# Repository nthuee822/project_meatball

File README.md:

# project_meatball

A custom three-wheel omnidirectional robot: radial-mount wheels driven by
FOC-controlled motors with magnetic angle encoders, steered by a Logitech F710
gamepad through a Raspberry Pi, with IMU-based orientation sensing and
custom PCBs and 3D-printed mechanical parts.

## Repository Layout

| Directory | Contents |
|---|---|
| [`controller/`](controller/) | Raspberry Pi Python controller: reads the gamepad, computes inverse kinematics for the three radial wheels, and streams motor commands over SPI (optionally fused with IMU data). |
| [`IMU/`](IMU/) | Standalone Python driver for the ICM-20948 9-axis IMU (accel/gyro/mag) over I2C on the Raspberry Pi, plus calibration and debug scripts. |
| [`stm32/`](stm32/) | STM32CubeIDE firmware projects for the per-wheel motor drivers: field-oriented control (`foc_v0`, `foc_v1`), AS5600 magnetic encoder angle measurement (`angle_measurement_test`, `angle_measurement_kalman`), ADC alignment testing, and a stepper/SPI test build. `common_lib/` holds the shared AS5600 driver. |
| [`hardware/`](hardware/) | KiCad PCB projects: current-sense simulation, the `ht7k1401` breakout board, and a shared component library. |
| [`3d_model/`](3d_model/) | FreeCAD/3MF models for printed parts — motor holders, hall-sensor holders/washers, magnet mold, and corner brackets. |
| [`architecture/`](architecture/) | System architecture diagrams (drawio source + exported PDF). |
| [`images/`](images/) | Reference photos and renders. |

## System Overview

```
F710 gamepad --USB--> Raspberry Pi (controller/) --SPI--> STM32 motor drivers (stm32/foc_*)
                              ^                                    |
                              |                                    v
                        IMU/ (ICM-20948)                 AS5600 encoder + motor
```

Each wheel's STM32 board runs closed-loop FOC using position feedback from an
AS5600 magnetic encoder (angle read directly, or Kalman-filtered — see
`stm32/angle_measurement_kalman`). The Raspberry Pi computes per-wheel speed/
direction from gamepad input via radial-mount inverse kinematics and sends
them as fixed-format SPI frames; see [`controller/README.md`](controller/README.md)
for the protocol and kinematics details.

## Getting Started

### Python Environment (uv)

All Python code (`controller/`, `IMU/`, `stm32/*/` scripts) shares one
environment managed by [uv](https://docs.astral.sh/uv/), defined in
`pyproject.toml` and pinned by `uv.lock`. It lives in `.venv/` at the repo
root and does not touch your system Python.

```bash
# 1. Install uv (once per machine)
curl -LsSf https://astral.sh/uv/install.sh | sh          # Linux / macOS
# powershell -c "irm https://astral.sh/uv/install.ps1 | iex"   # Windows

# 2. Create .venv and install dependencies (re-run after pulling changes)
uv sync

# 3. Run scripts through uv (works from any subdirectory)
cd controller && uv run python run_test.py
```

Hardware libraries (`smbus2`, `spidev`, `rpi-lgpio` which provides
`RPi.GPIO`) are only installed on Raspberry Pi (Linux ARM64). On a laptop,
`uv sync` skips them, so you can still run the hardware-independent parts
(kinematics, gamepad/keyboard input, plotting).

On the Raspberry Pi, `rpi-lgpio` is compiled from source, so install the build
dependencies once before the first `uv sync`:

```bash
sudo apt install -y swig liblgpio-dev
```

To add a dependency: `uv add <package>` (commit both `pyproject.toml` and `uv.lock`).

### Subsystems

Each subsystem has its own setup instructions:

- Robot controller (gamepad + kinematics + SPI): [`controller/README.md`](controller/README.md)
- IMU driver and wiring/calibration: [`IMU/README.md`](IMU/README.md)
- STM32 firmware: open the relevant `.ioc` project in STM32CubeIDE (each project directory is self-contained with CMake presets for building outside the IDE).
- PCB designs: open the `.kicad_pro` files in KiCad.
- 3D models: open the `.FCStd` files in FreeCAD; `.3mf` files are ready to slice/print.

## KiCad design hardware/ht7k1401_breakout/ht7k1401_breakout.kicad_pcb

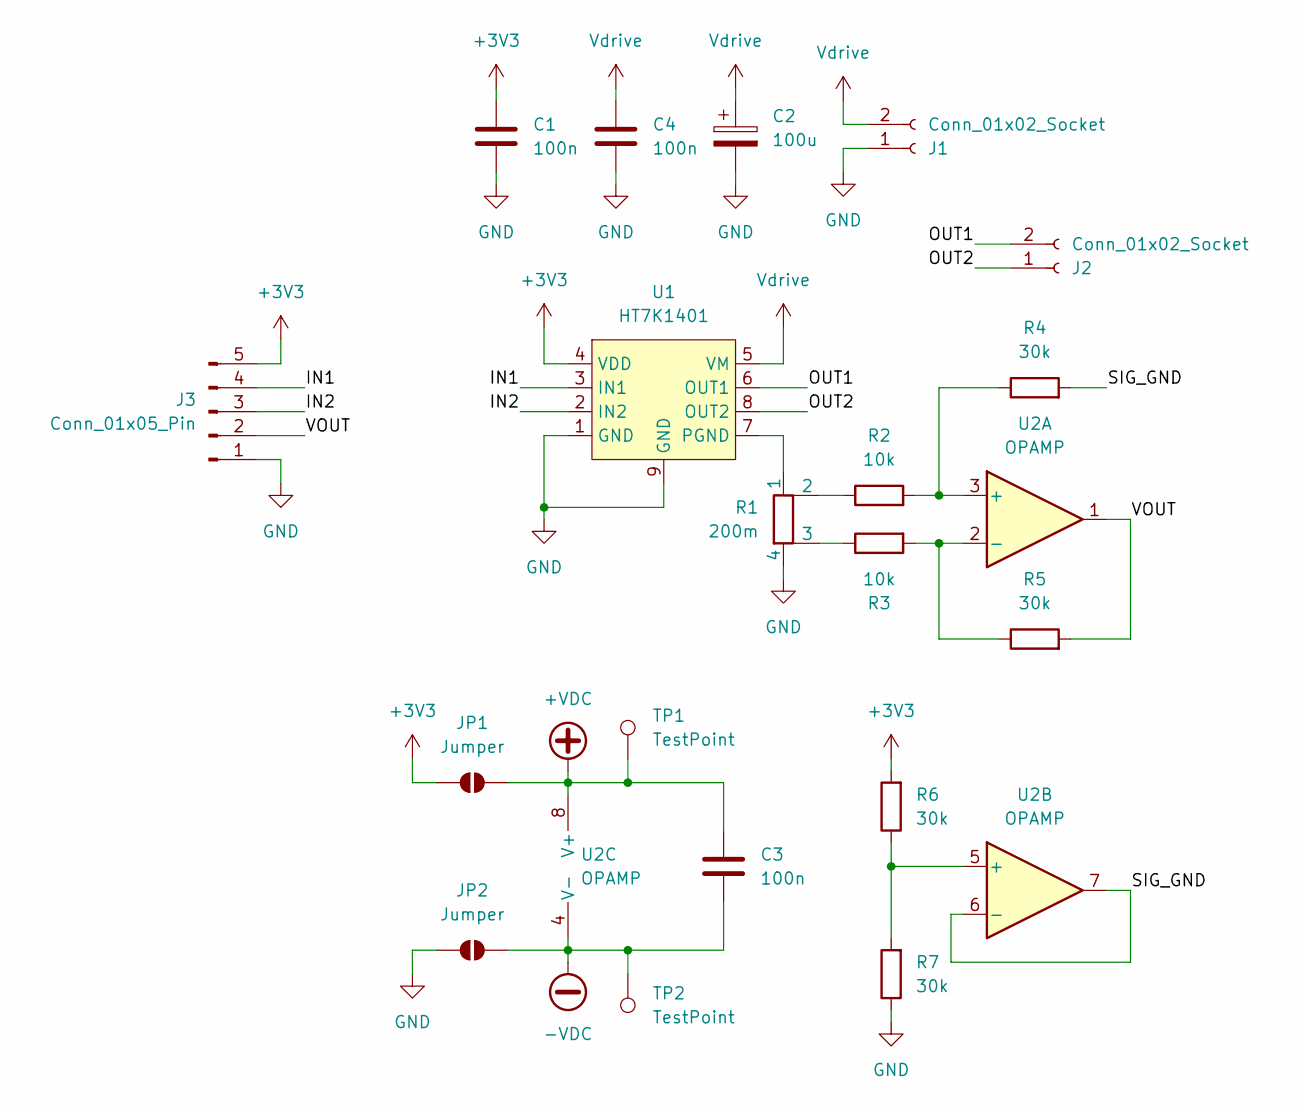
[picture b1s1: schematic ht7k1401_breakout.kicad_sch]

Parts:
C1, C3, C4: 100n; C_0805_2012Metric_Pad1.18x1.45mm_HandSolder
C2: 100u; CP_Radial_D6.3mm_P2.50mm
J1, J2: Conn_01x02_Socket; TerminalBlock_MaiXu_MX126-5.0-02P_1x02_P5.00mm
J3: Conn_01x05_Pin; PinHeader_1x05_P2.54mm_Vertical
JP1, JP2: Jumper; SolderJumper-2_P1.3mm_Open_RoundedPad1.0x1.5mm
R1: 200m; 2512_shunt
R2, R3: 10k; R_0805_2012Metric_Pad1.20x1.40mm_HandSolder
R4, R5, R6, R7: 30k; R_0805_2012Metric_Pad1.20x1.40mm_HandSolder
TP1, TP2: TestPoint; TestPoint_THTPad_D1.5mm_Drill0.7mm
U1: HT7K1401; HSOP-8-1EP_3.9x4.9mm_P1.27mm_EP2.41x3.1mm
U2: OPAMP; SOIC-8_3.9x4.9mm_P1.27mm

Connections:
+3V3: C1.1, J3.5, JP1.1 (A), R6.2, U1.4 (VDD)
+VDC: C3.1, JP1.2 (B), TP1.1, U2.8 (V+)
-VDC: C3.2, JP2.2 (B), TP2.1, U2.4 (V-)
/IN1: J3.4, U1.3 (IN1)
/IN2: J3.3, U1.2 (IN2)
/OUT1: J2.2, U1.6 (OUT1)
/OUT2: J2.1, U1.8 (OUT2)
/SIG_GND: R4.2, U2.6 (-), U2.7
/VOUT: J3.2, R5.2, U2.1
GND: C1.2, C2.2, C4.2, J1.1, J3.1, JP2.1 (A), R1.4, R7.1, U1.1 (GND), U1.9 (GND)
unnamed: R1.2, R2.1
unnamed: R1.3, R3.1
unnamed: R1.1, U1.7 (PGND)
unnamed: R2.2, R4.1, U2.3 (+)
unnamed: R3.2, R5.1, U2.2 (-)
unnamed: R6.1, R7.2, U2.5 (+)
Vdrive: C2.1, C4.1, J1.2, U1.5 (VM)

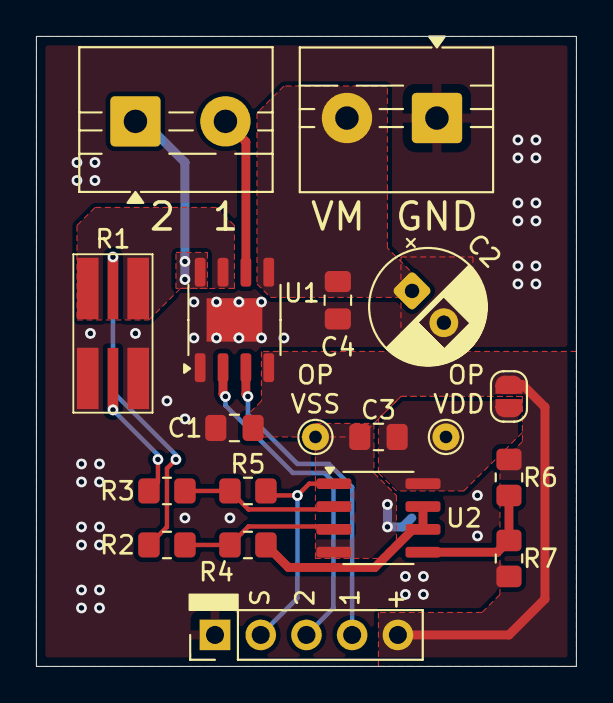
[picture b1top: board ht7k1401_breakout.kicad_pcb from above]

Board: 2 copper layers, 30.0 x 35.0 mm, 20 parts (1 on the bottom side), 17 nets.

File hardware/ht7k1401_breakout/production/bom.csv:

Designator,Footprint,Quantity,Value,LCSC Part #
"C1, C3, C4",0805,3,100n,
C2,CP_Radial_D6.3mm_P2.50mm,1,100u,
"J1, J2",TerminalBlock_MaiXu_MX126-5.0-02P_1x02_P5.00mm,2,Conn_01x02_Socket,
J3,PinHeader_1x05_P2.54mm_Vertical,1,Conn_01x05_Pin,
R1,2512_shunt,1,200m,
"R2, R3",0805,2,10k,
"R4, R5, R6, R7",0805,4,30k,
"TP1, TP2",TestPoint_THTPad_D1.5mm_Drill0.7mm,2,TestPoint,
U1,HSOP-8-1EP_3.9x4.9mm_P1.27mm_EP2.41x3.1mm,1,HT7K1401,
U2,SOIC-8_3.9x4.9mm_P1.27mm,1,OPAMP,
